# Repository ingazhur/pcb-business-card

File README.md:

# pcb-business-card

A custom-made contact PCB card that redirects to my LinkedIn page when tapping on a phone. 
The card has an NFC chip and an LED that lights up upon contact.

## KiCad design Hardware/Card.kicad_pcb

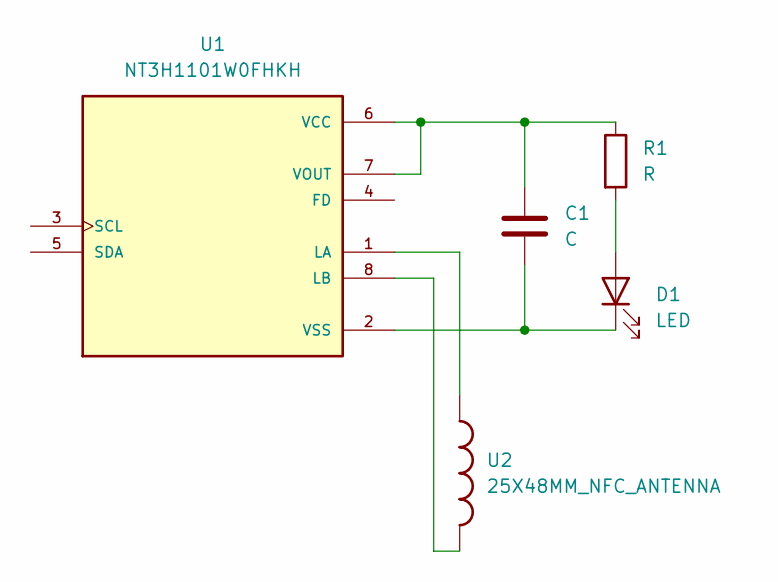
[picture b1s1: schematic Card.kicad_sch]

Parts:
C1: C; C_0402_1005Metric
D1: LED; LED_0603_1608Metric
R1: R; R_0402_1005Metric
U1: NT3H1101W0FHKH; IC_NT3H1101W0FHKH; PARTREV 3.3
U2: 25X48MM_NFC_ANTENNA

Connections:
unnamed: C1.1, R1.1, U1.6 (VCC), U1.7 (VOUT)
unnamed: C1.2, D1.1 (K), U1.2 (VSS)
unnamed: D1.2 (A), R1.2
unnamed: U1.1 (LA), U2.P$1
unnamed: U1.8 (LB), U2.P$2

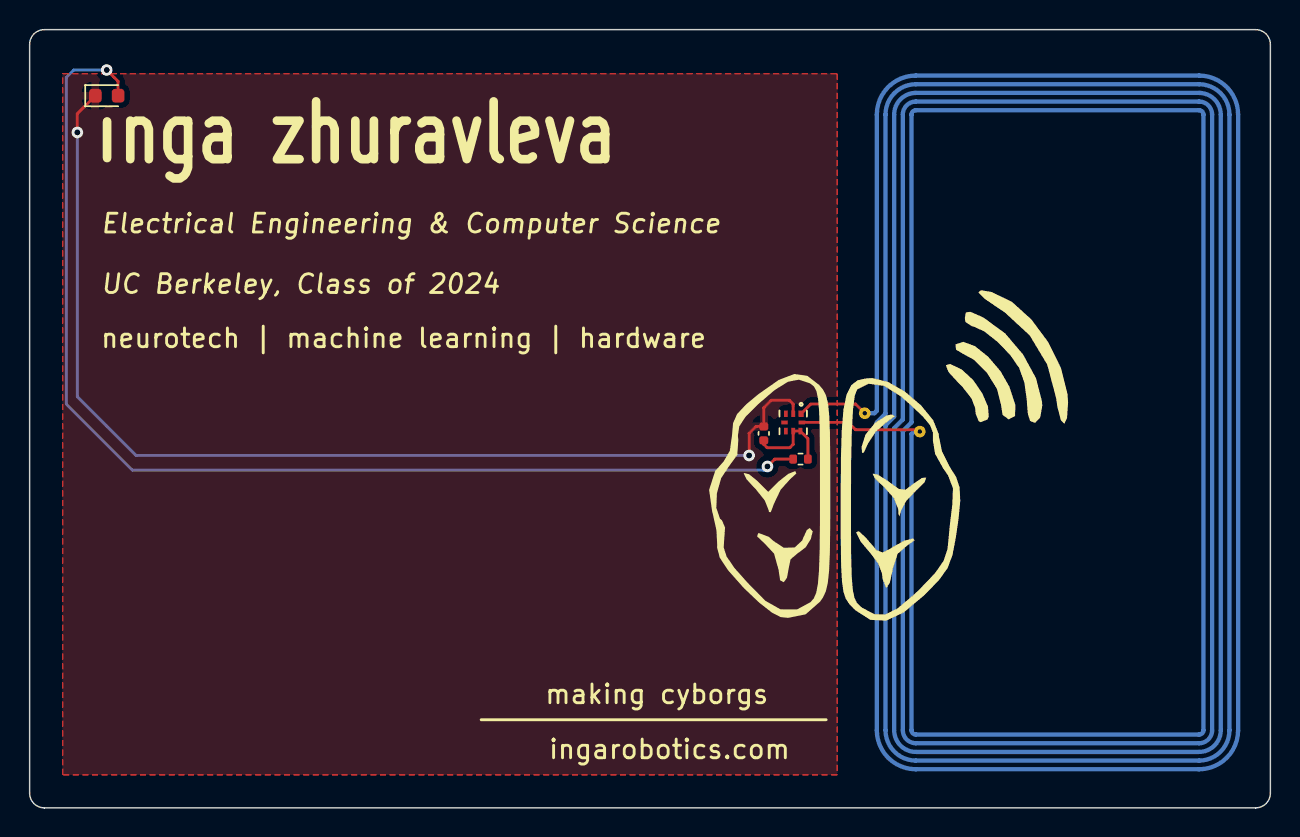
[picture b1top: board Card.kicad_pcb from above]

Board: 2 copper layers, 85.9 x 53.8 mm, 5 parts (1 on the bottom side), 5 nets.

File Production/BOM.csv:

"Id";"Designator";"Package";"Quantity";"Designation";"Supplier and ref";
1;"C1";"C_0402_1005Metric";1;"C";;;
2;"R1";"R_0402_1005Metric";1;"R";;;
3;"G***";"LOGO";1;"LOGO";;;
4;"D1";"LED_0603_1608Metric";1;"LED";;;
5;"U1";"IC_NT3H1101W0FHKH";1;"NT3H1101W0FHKH";;;
6;"U2";"25X48MM_NFC_ANTENNA";1;"25X48MM_NFC_ANTENNA";;;

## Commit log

2022-05-28 uploading KiCad files
